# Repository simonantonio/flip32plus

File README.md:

# twist32+

This should be pin compatible with the naze32/flip32+ but will require modified firmware to drive the MPU9120

Newly laid out PCB based on the MPU9250 (accelerometer, gyroscope, magnetometer)
MS5611-01BA - Barometer 

Designed to fit the standard 36mm footprint of other flight controllers.

Power via ESC 1.

Makes use of JST SH connectors to take up less board space and make wiring tidier

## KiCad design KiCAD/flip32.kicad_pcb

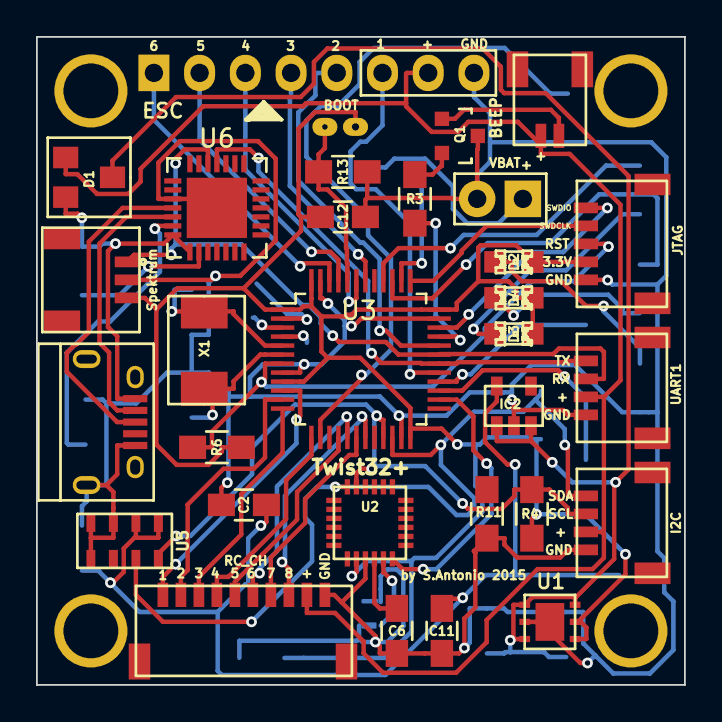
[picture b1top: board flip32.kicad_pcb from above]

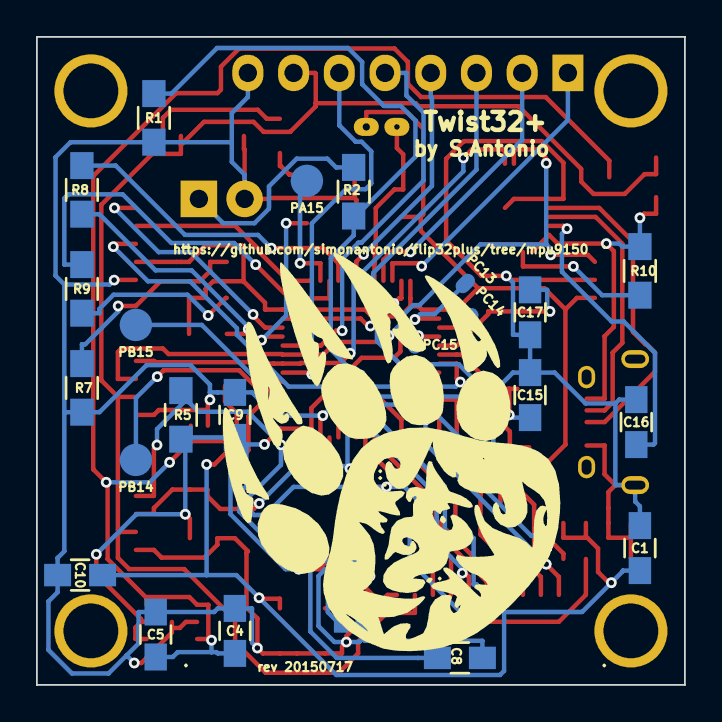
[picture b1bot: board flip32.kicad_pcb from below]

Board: 2 copper layers, 36.0 x 36.0 mm, 59 parts (24 on the bottom side), 54 nets.

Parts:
BEEP: BEEPER; Pin_Header_Straight_1x02
BOOT: BOOT; Pin_Header_Straight_1x02
C1, C2, C4, C5, C6, C9, C12, C16: 0.1uF; C_0805_HandSoldering
C8: 10uF; C_0805_HandSoldering
C10, C11, C15, C17: C; C_0805_HandSoldering
CON1: USB; USB_Micro-B
D1: BAV23C; GS3
D2: B; LED-0805
D3: R; LED-0805
D4: G; LED-0805
ESC: ESC OUT; Pin_Header_Straight_1x08
FSYNC-MPU: MPU-JMP; NetTie-I_Connected
I2C: I2C; Pin_Header_Straight_1x04
IC2: MIC5205; SOT-23-5
JP1: MPU-JMP; NetTie-I_Connected
JTAG: JTAG; Pin_Header_Straight_1x05
MNT1, MNT2, MNT3, MNT4: 1pin
PA15: TP; 1pin
PB14, PB15: TP; 1pin
PC13, PC14, PC15: UU5; 1pin
Q1: MMBT29; SOT-23
R1: 11K; R_0805_HandSoldering
R2, R4, R5: 1K; R_0805_HandSoldering
R3: 100; R_0805_HandSoldering
R6, R10: 10k; R_0805_HandSoldering
R7, R8, R9: R; R_0805_HandSoldering
R11, R13: 1k; R_0805_HandSoldering
RC_CH: RECV CHANNELS; Pin_Header_Straight_1x10
Spektrum: Spektrum Satellite Receiver; Pin_Header_Straight_1x03
U1: LP38691; sc70-5
U2: MPU-9250; QFN-24-1EP_3x3mm_Pitch0.4mm
U3: STM32F103CB; LQFP-48_7x7mm_Pitch0.5mm
U5: MS5611-01BA; SOIC-8_3.9x4.9mm_Pitch1.27mm
U6: CP2102; QFN-28-1EP_5x5mm_Pitch0.5mm
UART1: UART 1; Pin_Header_Straight_1x04
VBAT: VBAT; Socket_Strip_Straight_1x02
X1: 8MHZ; Q_49U3HMS

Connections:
/BOOT0: BOOT.1, R13.1, U3.44
/BOOT1: R11.1, U3.20
/LED0: R8.2, U3.40
/LED1: R9.2, U3.39
/MPU_INT: U2.12, U3.26
/NRST: JTAG.3, R6.2, U3.7
/OSC_IN: C17.1, U3.5, X1.2
/OSC_OUT: C15.1, U3.6, X1.1
/POWER_ADC: R1.2, R2.1, U3.14
/PWM1: ESC.6, U3.29
/PWM2: ESC.5, U3.32
/PWM3: ESC.4, U3.42
/PWM4: ESC.3, U3.43
/PWM5: ESC.2, U3.45
/PWM6: ESC.1, U3.46
/RC_CH1: RC_CH.1, U3.10
/RC_CH2: RC_CH.2, U3.11
/RC_CH3: RC_CH.3, U3.12
/RC_CH4: RC_CH.4, U3.13
/RC_CH5: RC_CH.5, U3.16
/RC_CH6: RC_CH.6, U3.17
/RC_CH7: RC_CH.7, U3.18
/RC_CH8: RC_CH.8, U3.19
/RX0: Spektrum.1, U3.31, U6.26, UART1.2
/SCL: I2C.2, R4.2, U2.23, U3.21, U5.8
/SDA: I2C.1, R5.2, U2.24, U3.22, U5.7
/SWDCLK: JTAG.2, U3.37
/SWDIO: JTAG.1, U3.34
/TO_REGS: C4.1, C5.1, D1.3, IC2.1, IC2.3, U1.1, U1.3, U1.6
/TX0: U3.30, U6.25, UART1.1
/UU1: R3.1, U3.33
/UU2: PA15.1, U3.38
/UU3: PC13.1, U3.2
/UU4: PC14.1, U3.3
/UU5: PC15.1, U3.4
/UU7: PB14.1, U3.27
/UU8: PB15.1, U3.28
/VBUS: CON1.1, D1.2, R10.1, U6.7, U6.8
/VCC_IN: BEEP.1, D1.1, ESC.7, I2C.3, RC_CH.9, UART1.3
/VCC_SEN: C1.1, C2.1, C10.1, C11.1, IC2.5, U2.13, U5.1, U5.2
GND: C1.2, C2.2, C4.2, C5.2, C6.2, C8.2, C9.2, C10.2, C11.2, C12.2, C15.2, C16.2, C17.2, CON1.5, CON1.6, ESC.8, FSYNC-MPU.2, I2C.4, IC2.2, JP1.2, JTAG.5, Q1.3, R1.1, R7.2, R11.2, R13.2, RC_CH.10, Spektrum.2, U1.2, U1.7, U2.9, U2.18, U2.20, U3.8, U3.23, U3.35, U3.47, U5.3, U5.4, U5.5, U6.3, U6.29, UART1.4, VBAT.2
unnamed: R10.2, U6.9
unnamed: CON1.2, U6.5
unnamed: CON1.3, U6.4
unnamed: C6.1, U2.10
unnamed: FSYNC-MPU.1, U2.11
unnamed: C16.1, U6.6
unnamed: D3.2, R8.1
unnamed: D4.2, R9.1
unnamed: D2.2, R7.1
unnamed: Q1.2, R3.2
unnamed: BEEP.2, Q1.1
unnamed: R2.2, VBAT.1
VCC: BOOT.2, C8.1, C9.1, C12.1, D2.1, D3.1, D4.1, JTAG.4, R4.1, R5.1, R6.1, Spektrum.3, U1.4, U1.5, U2.8, U2.22, U3.1, U3.9, U3.24, U3.36, U3.48

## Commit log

2015-07-14 My version of the schematic. Hopefully more readable than the crappy jpg version found online
2015-07-14 initial version of the flip32+ schematic and netlist in KiCAD
    Note that the footprints are not the same as the original board, there may also be slightly different part numbers, and a few more by pass caps.
2015-07-16 Removed unused accelormeter (MMA8452Q)
2015-07-17 Finished pcb layout for MPU9150
2015-07-17 fixed some missing labels
2015-07-17 updated readme for the project
2015-07-17 updated schematic pdf
2015-07-20 swapped from old mpu9150 to newer mpu9250
2015-07-20 redoing layout of traces for updated pinout of mpu9250
2015-07-20 pcb completed
2015-07-20 new gerbers for mpu9250
2015-07-21 optimize layout, reduced track length, reduced via count
2015-07-21 add gerbers zip
2015-07-21 add renders of board
2015-07-21 readme updated
2015-07-21 fixed paths to imgs
